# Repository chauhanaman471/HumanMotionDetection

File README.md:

# HumanMotionDetection

## Overview

This project implements Human Motion Detection using the IPM-165 CW Radar Module and the PSoC 5 LP Creator Board. It includes various components such as KiCad PCB Layout, an ADC Sampling State Machine on PSoC Creator, and FFT and CFAR Algorithm implementation in MATLAB. The project showcases the integration and end result of these components.

This work is part of the academic curriculum for the subject: System Driven Hardware Designing Lab.

## Project Structure

### 1. SDHD_Lab1_Lab2

Contains:
- **KiCad Layout**: PCB layout files for the analog and digital circuits.
- **KiCad Schematic**: Schematics of the analog and digital circuits.
- **PCB Design**: Built on a 4-layer PCB board with the following layers:
  - Signal (Analog)
  - Vcc
  - Ground
  - Signal (Digital)

### 2. PSOC+MATLAB

Contains:
- **PSoC Code**: Source code for the ADC sampling state machine. The code handles the sampling of radar signals and transmits the data to MATLAB via UART.
- **MATLAB Code**: FFT and CFAR algorithms are implemented to process the ADC samples. The FFT is performed on the samples, and the CFAR algorithm analyzes these samples against a threshold value to detect motion.

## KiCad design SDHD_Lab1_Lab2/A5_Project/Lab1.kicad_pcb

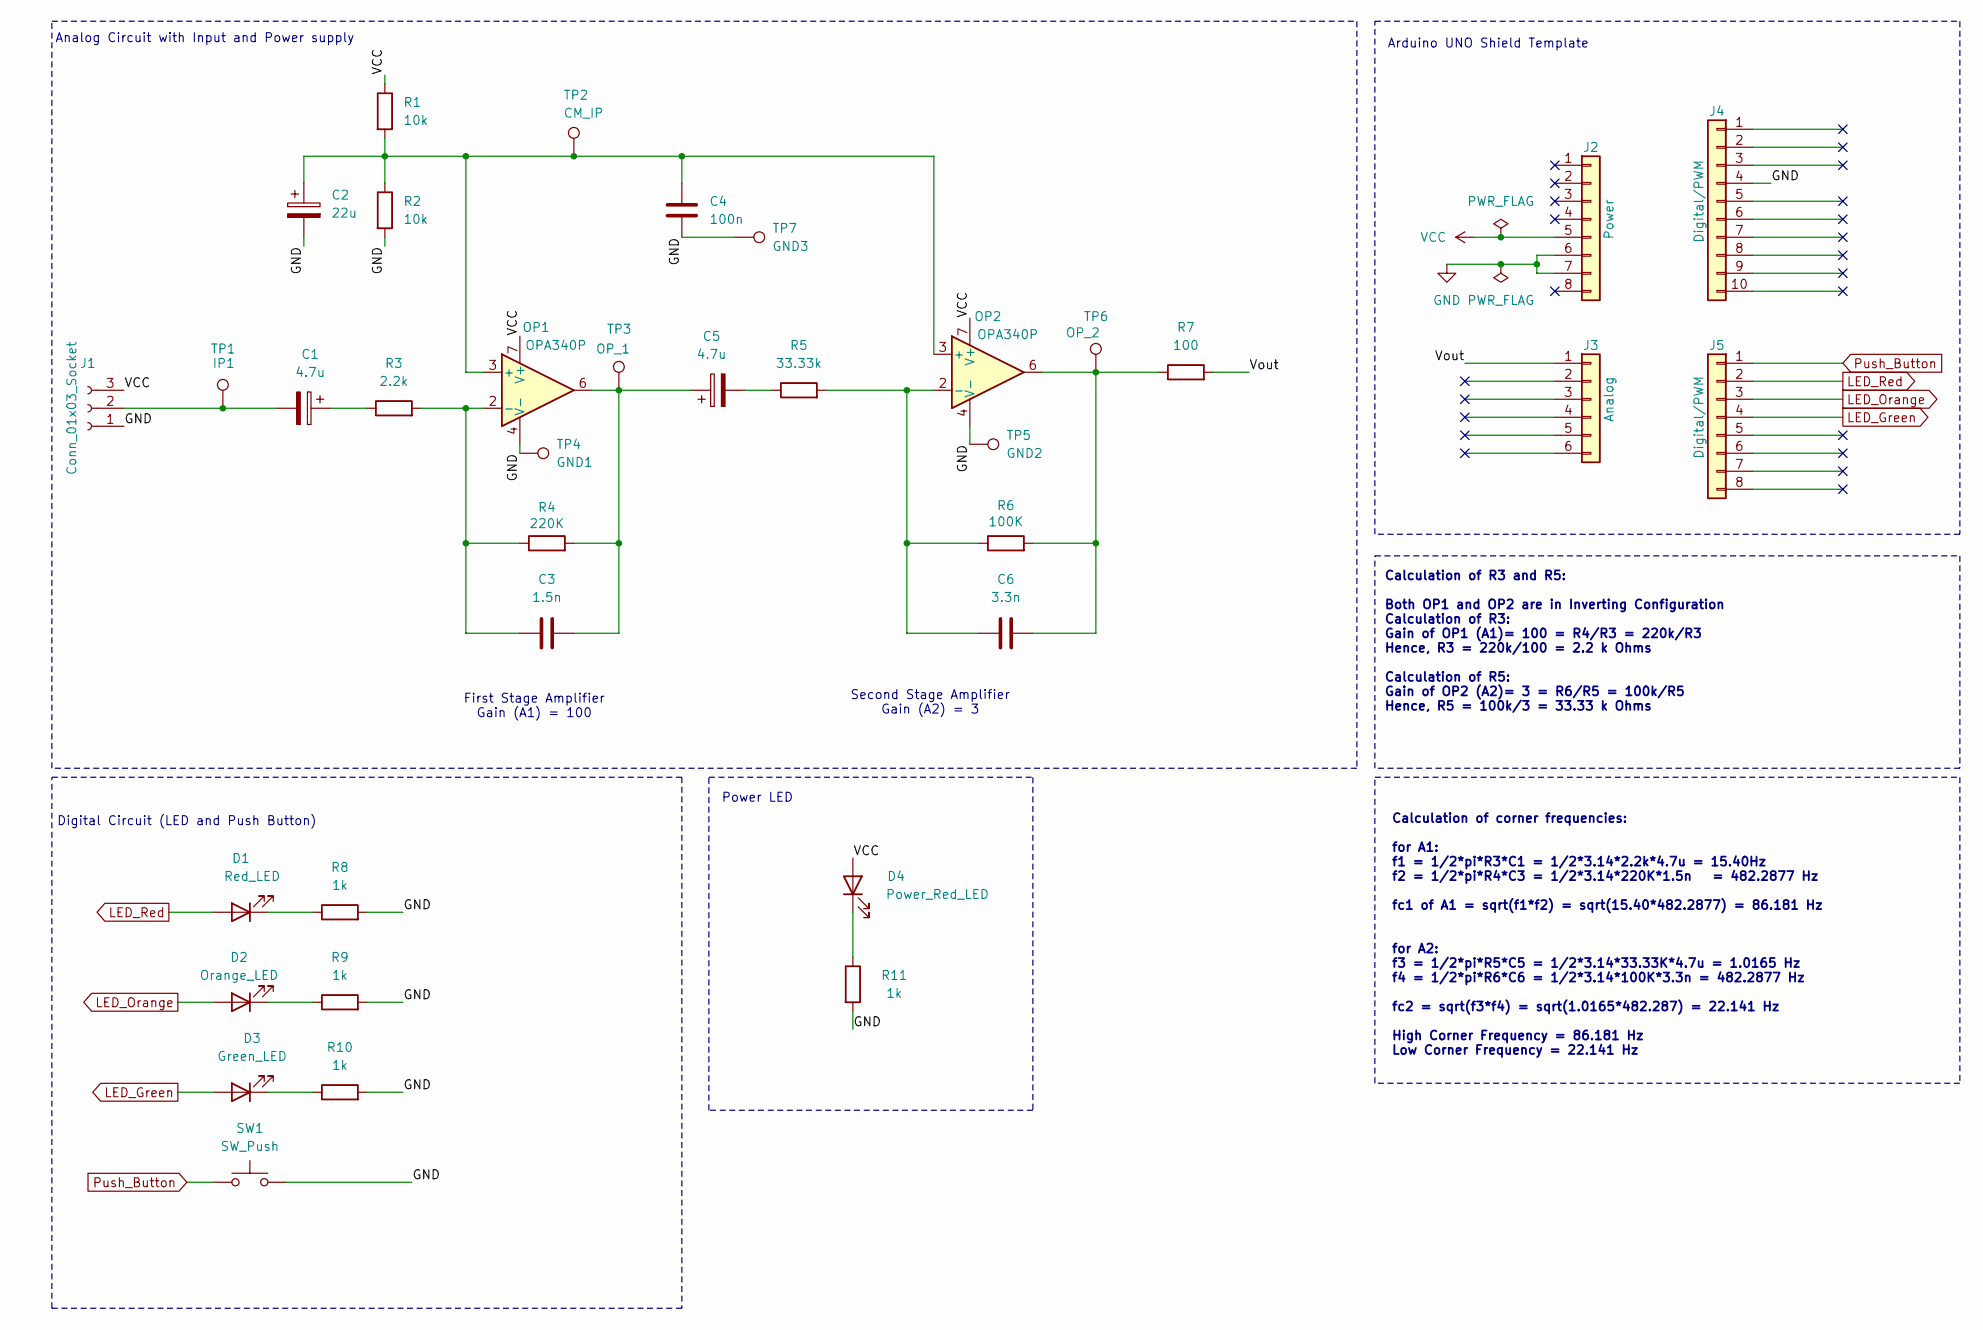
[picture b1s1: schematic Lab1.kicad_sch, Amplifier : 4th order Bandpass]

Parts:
C1, C5: 4.7u; CP_Radial_D5.0mm_P2.50mm
C2: 22u; CP_Radial_D5.0mm_P2.00mm
C3: 1.5n; C_Rect_L7.2mm_W7.2mm_P5.00mm_FKS2_FKP2_MKS2_MKP2
C4: 100n; C_Rect_L7.2mm_W2.5mm_P5.00mm_FKS2_FKP2_MKS2_MKP2
C6: 3.3n; C_Rect_L7.2mm_W7.2mm_P5.00mm_FKS2_FKP2_MKS2_MKP2
D1: Red_LED; LED_D5.0mm
D2: Orange_LED; LED_D5.0mm
D3: Green_LED; LED_D5.0mm
D4: Power_Red_LED; LED_D5.0mm
J1: Conn_01x03_Socket; PinSocket_1x03_P2.54mm_Horizontal
J2: Power; PinHeader_1x08_P2.54mm_Vertical
J3: Analog; PinHeader_1x06_P2.54mm_Vertical
J4: Digital/PWM; PinHeader_1x10_P2.54mm_Vertical
J5: Digital/PWM; PinHeader_1x08_P2.54mm_Vertical
OP1, OP2: OPA340P; DIP-8_W7.62mm
R1, R2: 10k; R_Axial_DIN0207_L6.3mm_D2.5mm_P10.16mm_Horizontal
R3: 2.2k; R_Axial_DIN0207_L6.3mm_D2.5mm_P10.16mm_Horizontal
R4: 220K; R_Axial_DIN0207_L6.3mm_D2.5mm_P10.16mm_Horizontal
R5: 33.33k; R_Axial_DIN0207_L6.3mm_D2.5mm_P10.16mm_Horizontal
R6: 100K; R_Axial_DIN0207_L6.3mm_D2.5mm_P10.16mm_Horizontal
R7: 100; R_Axial_DIN0207_L6.3mm_D2.5mm_P10.16mm_Horizontal
R8, R9, R10, R11: 1k; R_Axial_DIN0207_L6.3mm_D2.5mm_P10.16mm_Horizontal
SW1: SW_Push; SW_PUSH_6mm
TP1: IP1; PinHeader_1x01_P2.54mm_Vertical
TP2: CM_IP; PinHeader_1x01_P2.54mm_Vertical
TP3: OP_1; PinHeader_1x01_P2.54mm_Vertical
TP4: GND1; PinHeader_1x01_P2.54mm_Vertical
TP5: GND2; PinHeader_1x01_P2.54mm_Vertical
TP6: OP_2; PinHeader_1x01_P2.54mm_Vertical
TP7: GND3; PinHeader_1x01_P2.54mm_Vertical

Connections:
/Vout: J3.1, R7.2
GND: C2.2, C4.2, J1.1, J2.6, J2.7, J4.4, OP1.4 (V-), OP2.4 (V-), R2.2, R8.2, R9.2, R10.2, R11.2, SW1.2, TP4.1, TP5.1, TP7.1
LED_Green: D3.2 (A), J5.4
LED_Orange: D2.2 (A), J5.3
LED_Red: D1.2 (A), J5.2
unnamed: C1.1, R3.1
unnamed: C3.2, C5.1, OP1.6, R4.2, TP3.1
unnamed: C5.2, R5.1
unnamed: C6.2, OP2.6, R6.2, R7.1, TP6.1
unnamed: D1.1 (K), R8.1
unnamed: D2.1 (K), R9.1
unnamed: D3.1 (K), R10.1
unnamed: D4.1 (K), R11.1
unnamed: C1.2, J1.2, TP1.1
unnamed: C2.1, C4.1, OP1.3 (+), OP2.3 (+), R1.2, R2.1, TP2.1
unnamed: C3.1, OP1.2 (-), R3.2, R4.1
unnamed: C6.1, OP2.2 (-), R5.2, R6.1
Push_Button: J5.1, SW1.1
VCC: D4.2 (A), J1.3, J2.5, OP1.7 (V+), OP2.7 (V+), R1.1

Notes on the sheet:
Analog Circuit with Input and Power supply
Power LED
Arduino UNO Shield Template
Calculation of corner frequencies: for A1: f1 = 1/2*pi*R3*C1 = 1/2*3.14*2.2k*4.7u = 15.40Hz f2 = 1/2*pi*R4*C3 = 1/2*3.14*220K*1.5n = 482.2877 Hz fc1 of A1 = sqrt(f1*f2) = sqrt(15.40*482.2877) = 86.181 Hz for A2: f3 = 1/2*pi*R5*C5 = 1/2*3.14*33.33K*4.7u = 1.0165 Hz f4 = 1/2*pi*R6*C6 = 1/2*3.14*100K*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
First Stage Amplifier Gain (A1) = 100
Calculation of R3 and R5: Both OP1 and OP2 are in Inverting Configuration Calculation of R3: Gain of OP1 (A1)= 100 = R4/R3 = 220k/R3 Hence, R3 = 220k/100 = 2.2 k Ohms Calculation of R5: Gain of OP2 (A2)= 3 = R6/R5 = 100k/R5 Hence, R5 = 100k/3 = 33.33 k Ohms
Second Stage Amplifier Gain (A2) = 3
Digital Circuit (LED and Push Button)

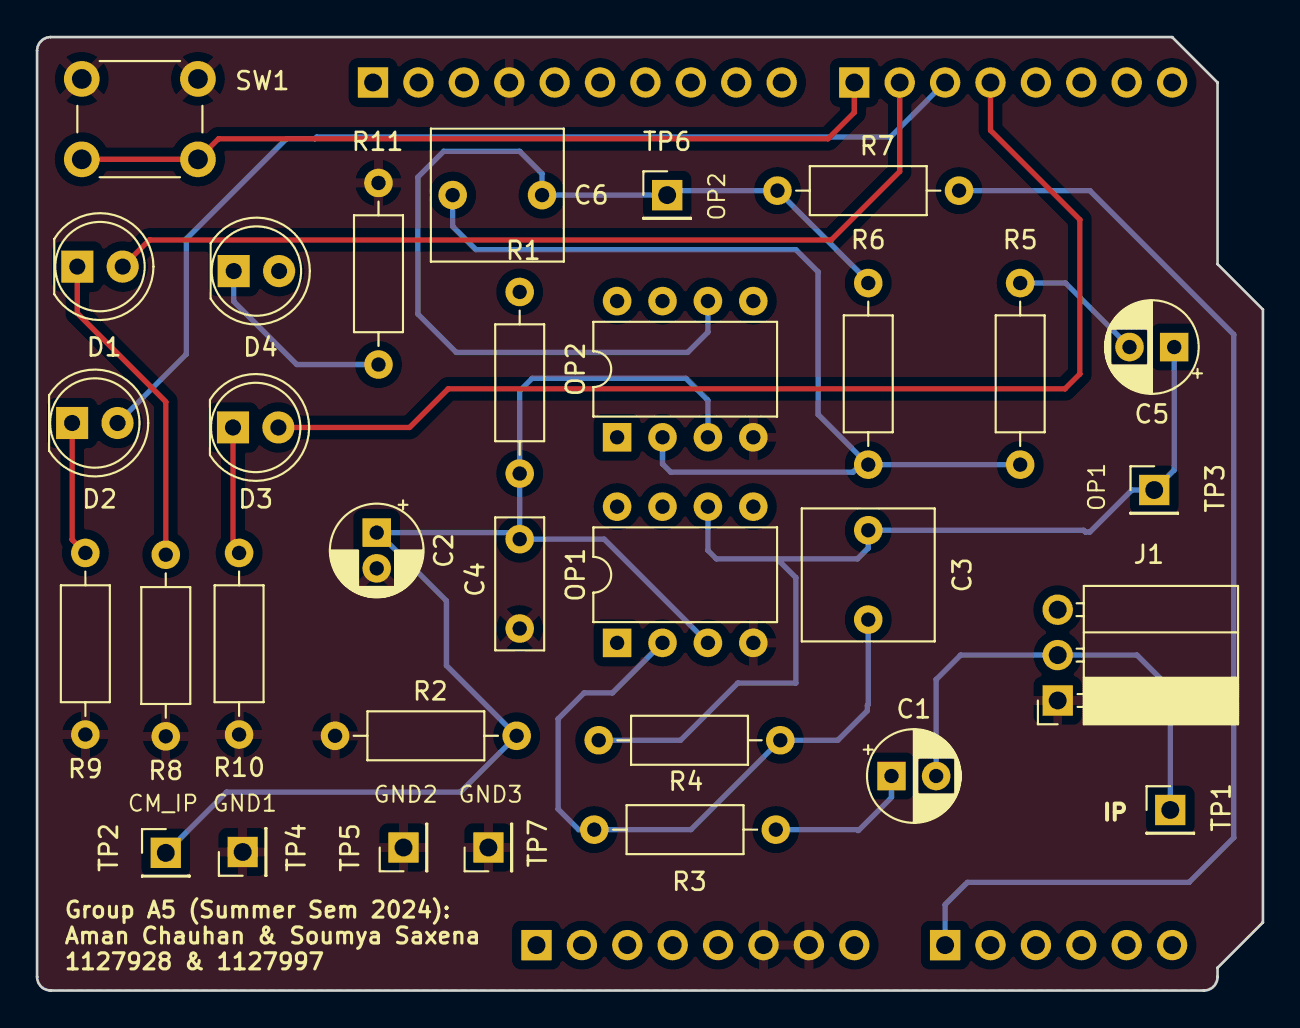
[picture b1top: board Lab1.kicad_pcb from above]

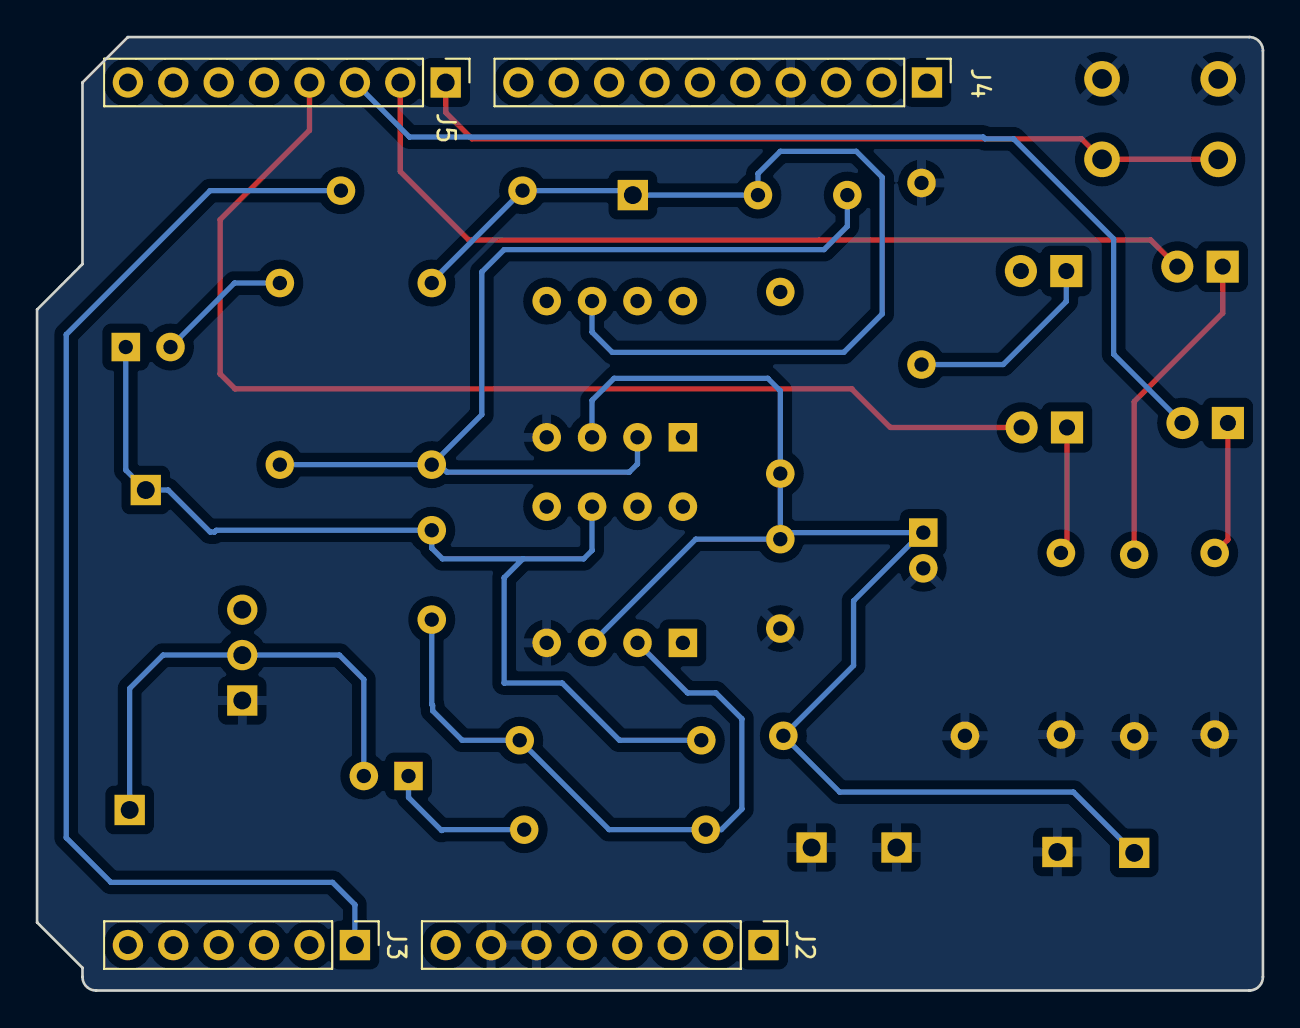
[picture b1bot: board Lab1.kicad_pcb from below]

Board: 4 copper layers, 68.6 x 53.3 mm, 36 parts (4 on the bottom side), 19 nets.

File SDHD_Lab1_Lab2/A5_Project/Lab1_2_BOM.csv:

"Reference","Value","Datasheet","Footprint","Qty","DNP"
"C1,C5","4.7u","~","Capacitor_THT:CP_Radial_D5.0mm_P2.50mm","2",""
"C2","22u","~","Capacitor_THT:CP_Radial_D5.0mm_P2.00mm","1",""
"C3","1.5n","~","Capacitor_THT:C_Rect_L7.2mm_W7.2mm_P5.00mm_FKS2_FKP2_MKS2_MKP2","1",""
"C4","100n","~","Capacitor_THT:C_Rect_L7.2mm_W2.5mm_P5.00mm_FKS2_FKP2_MKS2_MKP2","1",""
"C6","3.3n","~","Capacitor_THT:C_Rect_L7.2mm_W7.2mm_P5.00mm_FKS2_FKP2_MKS2_MKP2","1",""
"D1","Red_LED","~","LED_THT:LED_D5.0mm","1",""
"D2","Orange_LED","~","LED_THT:LED_D5.0mm","1",""
"D3","Green_LED","~","LED_THT:LED_D5.0mm","1",""
"D4","Power_Red_LED","~","LED_THT:LED_D5.0mm","1",""
"J1","Conn_01x03_Socket","~","Connector_PinSocket_2.54mm:PinSocket_1x03_P2.54mm_Horizontal","1",""
"J2","Power","","Connector_PinHeader_2.54mm:PinHeader_1x08_P2.54mm_Vertical","1",""
"J3","Analog","~","Connector_PinHeader_2.54mm:PinHeader_1x06_P2.54mm_Vertical","1",""
"J4,J5","Digital/PWM","","-- mixed values --","2",""
"OP1,OP2","OPA340P","http://www.ti.com/lit/ds/symlink/opa340.pdf","Package_DIP:DIP-8_W7.62mm","2",""
"R1,R2","10k","~","Resistor_THT:R_Axial_DIN0207_L6.3mm_D2.5mm_P10.16mm_Horizontal","2",""
"R3","2.2k","~","Resistor_THT:R_Axial_DIN0207_L6.3mm_D2.5mm_P10.16mm_Horizontal","1",""
"R4","220K","~","Resistor_THT:R_Axial_DIN0207_L6.3mm_D2.5mm_P10.16mm_Horizontal","1",""
"R5","33.33k","~","Resistor_THT:R_Axial_DIN0207_L6.3mm_D2.5mm_P10.16mm_Horizontal","1",""
"R6","100K","~","Resistor_THT:R_Axial_DIN0207_L6.3mm_D2.5mm_P10.16mm_Horizontal","1",""
"R7","100","~","Resistor_THT:R_Axial_DIN0207_L6.3mm_D2.5mm_P10.16mm_Horizontal","1",""
"R8,R9,R10,R11","1k","~","Resistor_THT:R_Axial_DIN0207_L6.3mm_D2.5mm_P10.16mm_Horizontal","4",""
"SW1","SW_Push","~","Button_Switch_THT:SW_PUSH_6mm","1",""
"TP1","IP1","~","Connector_PinHeader_2.54mm:PinHeader_1x01_P2.54mm_Vertical","1",""
"TP2","CM_IP","~","Connector_PinHeader_2.54mm:PinHeader_1x01_P2.54mm_Vertical","1",""
"TP3","OP_1","~","Connector_PinHeader_2.54mm:PinHeader_1x01_P2.54mm_Vertical","1",""
"TP4","GND1","~","Connector_PinHeader_2.54mm:PinHeader_1x01_P2.54mm_Vertical","1",""
"TP5","GND2","~","Connector_PinHeader_2.54mm:PinHeader_1x01_P2.54mm_Vertical","1",""
"TP6","OP_2","~","Connector_PinHeader_2.54mm:PinHeader_1x01_P2.54mm_Vertical","1",""
"TP7","GND3","~","Connector_PinHeader_2.54mm:PinHeader_1x01_P2.54mm_Vertical","1",""

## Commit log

2024-08-14 Initial commit of Human Motion Detection project
2024-08-14 Add NewFolder with initial files
